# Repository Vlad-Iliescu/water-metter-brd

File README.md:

# water-metter-brd 

full board for capturing water meter image and sending it via wi-fi

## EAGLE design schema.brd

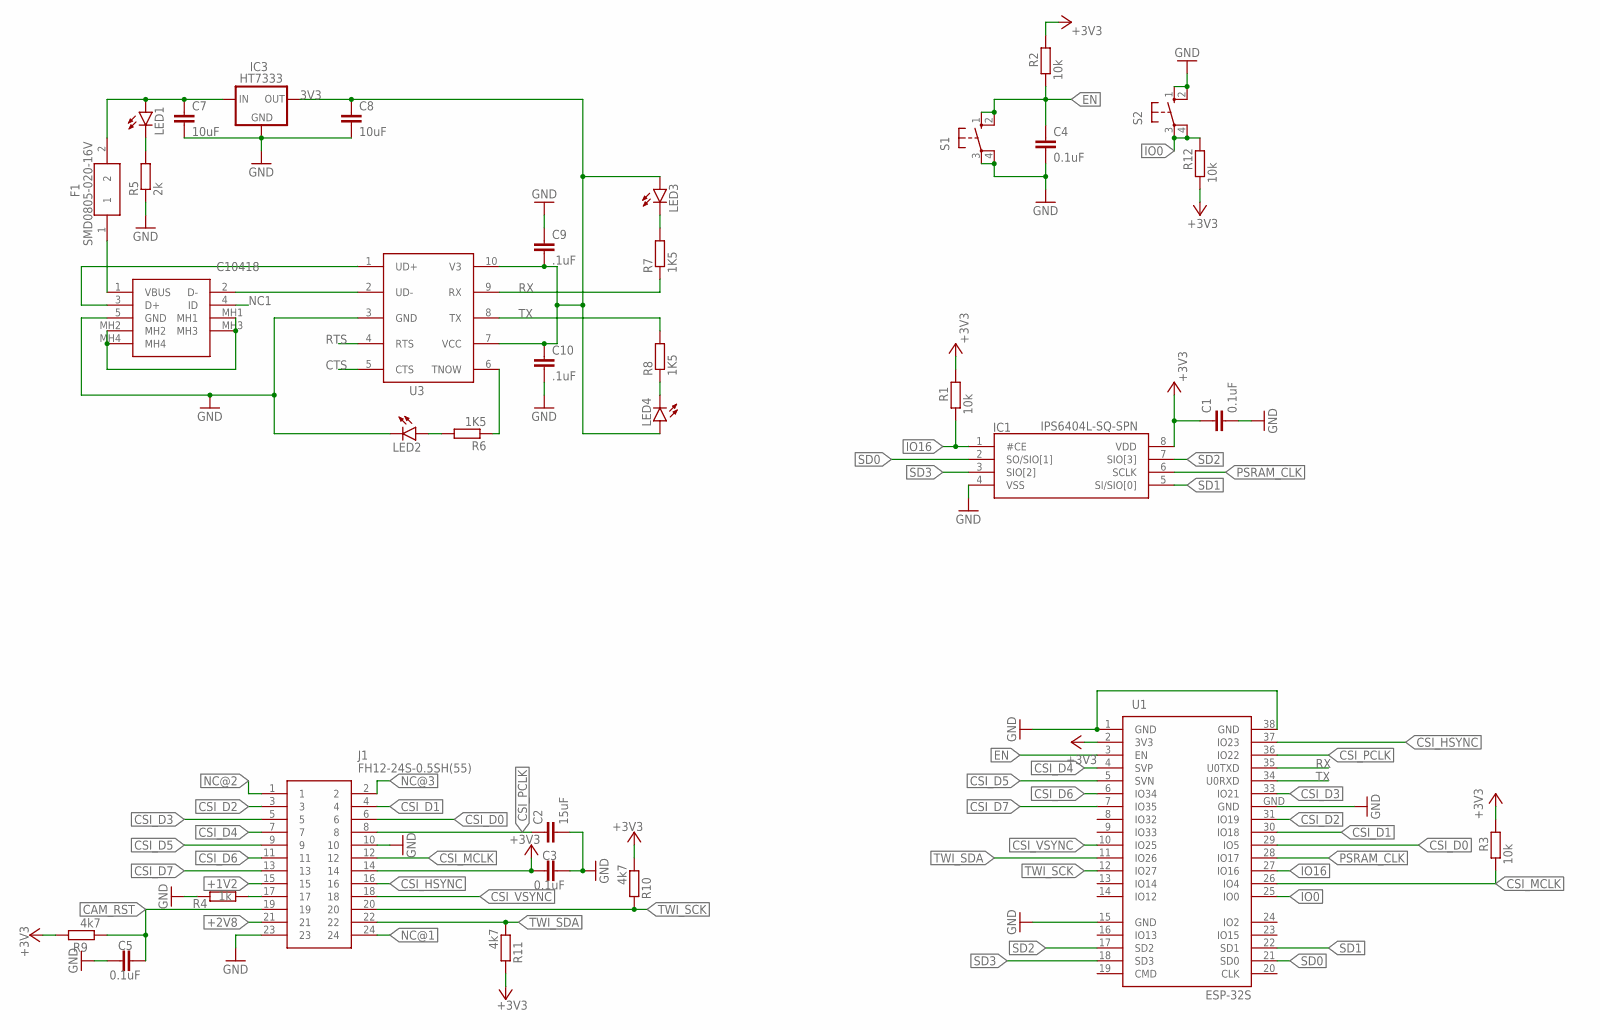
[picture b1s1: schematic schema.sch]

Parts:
C1, C3, C4, C5: 0.1uF; C0805
C2: 15uF; C0805
C7, C8: 10uF; C0805
C9, C10: .1uF; C0805
F1: SMD0805-020-16V; FUSC2114X100N
IC1: IPS6404L-SQ-SPN; SOIC127P600X175-8N
IC3: HT7333; SOT-89
J1: FH12-24S-0.5SH(55)
J3: C10418
LED1, LED2, LED3, LED4: LEDCHIP-LED0805; CHIP-LED0805
R1, R2, R3, R12: 10k; R0805
R4: 1k; R0805
R5: 2k; R0805
R6, R7, R8: 1K5; R0805
R9, R10, R11: 4k7; R0805
S1, S2: 10-XX; B3F-10XX
U1: ESP-32S
U3: CH340ESMD; MSOP10

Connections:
3V3: C8.1, C9.2, C10.1, IC3.1 (OUT), LED3.A, LED4.A, U3.7 (VCC), U3.10 (V3)
5V-USB: F1.1, J3.1 (VBUS)
+1V2: J1.15
+2V8: J1.21
+3V3: C1.1, C3.1, IC1.8 (VDD), J1.14, R1.2, R2.2, R3.2, R9.2, R10.1, R11.2, R12.1, U1.2 (3V3)
+5V1: C7.1, F1.2, IC3.3 (IN), IC3.4 (IN), LED1.A
CAM_RST: C5.2, J1.19, R9.1
CSI_D0: J1.6, U1.29 (IO5)
CSI_D1: J1.4, U1.30 (IO18)
CSI_D2: J1.3, U1.31 (IO19)
CSI_D3: J1.5, U1.33 (IO21)
CSI_D4: J1.7, U1.4 (SVP)
CSI_D5: J1.9, U1.5 (SVN)
CSI_D6: J1.11, U1.6 (IO34)
CSI_D7: J1.13, U1.7 (IO35)
CSI_HSYNC: J1.16, U1.37 (IO23)
CSI_MCLK: J1.12, R3.1, U1.26 (IO4)
CSI_PCLK: C2.1, J1.8, U1.36 (IO22)
CSI_VSYNC: J1.18, U1.10 (IO25)
CTS: U3.5 (CTS)
D+1: J3.3 (D+), U3.1 (UD+)
D-1: J3.2 (D-), U3.2 (UD-)
EN: C4.1, R2.1, S1.1 (S), S1.2 (S1), U1.3 (EN)
GND: C1.2, C2.2, C3.2, C4.2, C5.1, C7.2, C8.2, C9.1, C10.2, IC1.4 (VSS), IC3.2 (GND), J1.10, J1.23, J3.5 (GND), LED2.C, R4.2, R5.1, S1.3, S1.4 (P1), S2.1 (S), S2.2 (S1), U1.1 (GND), U1.15 (GND), U1.38 (GND), U1.GND, U3.3 (GND)
IO0: R12.2, S2.3, S2.4 (P1), U1.25 (IO0)
IO16: IC1.1 (#CE), R1.1, U1.27 (IO16)
MH: J3.MH1, J3.MH2, J3.MH3, J3.MH4
unnamed: J1.17, R4.1
unnamed: LED1.C, R5.2
unnamed: R6.1, U3.6 (TNOW)
unnamed: LED2.A, R6.2
unnamed: LED3.C, R7.2
unnamed: LED4.C, R8.1
NC1: J3.4 (ID)
NC@1: J1.24
NC@2: J1.1
NC@3: J1.2
PSRAM_CLK: IC1.6 (SCLK), U1.28 (IO17)
RTS: U3.4 (RTS)
RX: R7.1, U1.35 (U0TXD), U3.9 (RX)
SD0: IC1.2 (SO/SIO[1]), U1.21 (SD0)
SD1: IC1.5 (SI/SIO[0]), U1.22 (SD1)
SD2: IC1.7 (SIO[3]), U1.17 (SD2)
SD3: IC1.3 (SIO[2]), U1.18 (SD3)
TWI_SCK: J1.20, R10.2, U1.12 (IO27)
TWI_SDA: J1.22, R11.1, U1.11 (IO26)
TX: R8.2, U1.34 (U0RXD), U3.8 (TX)

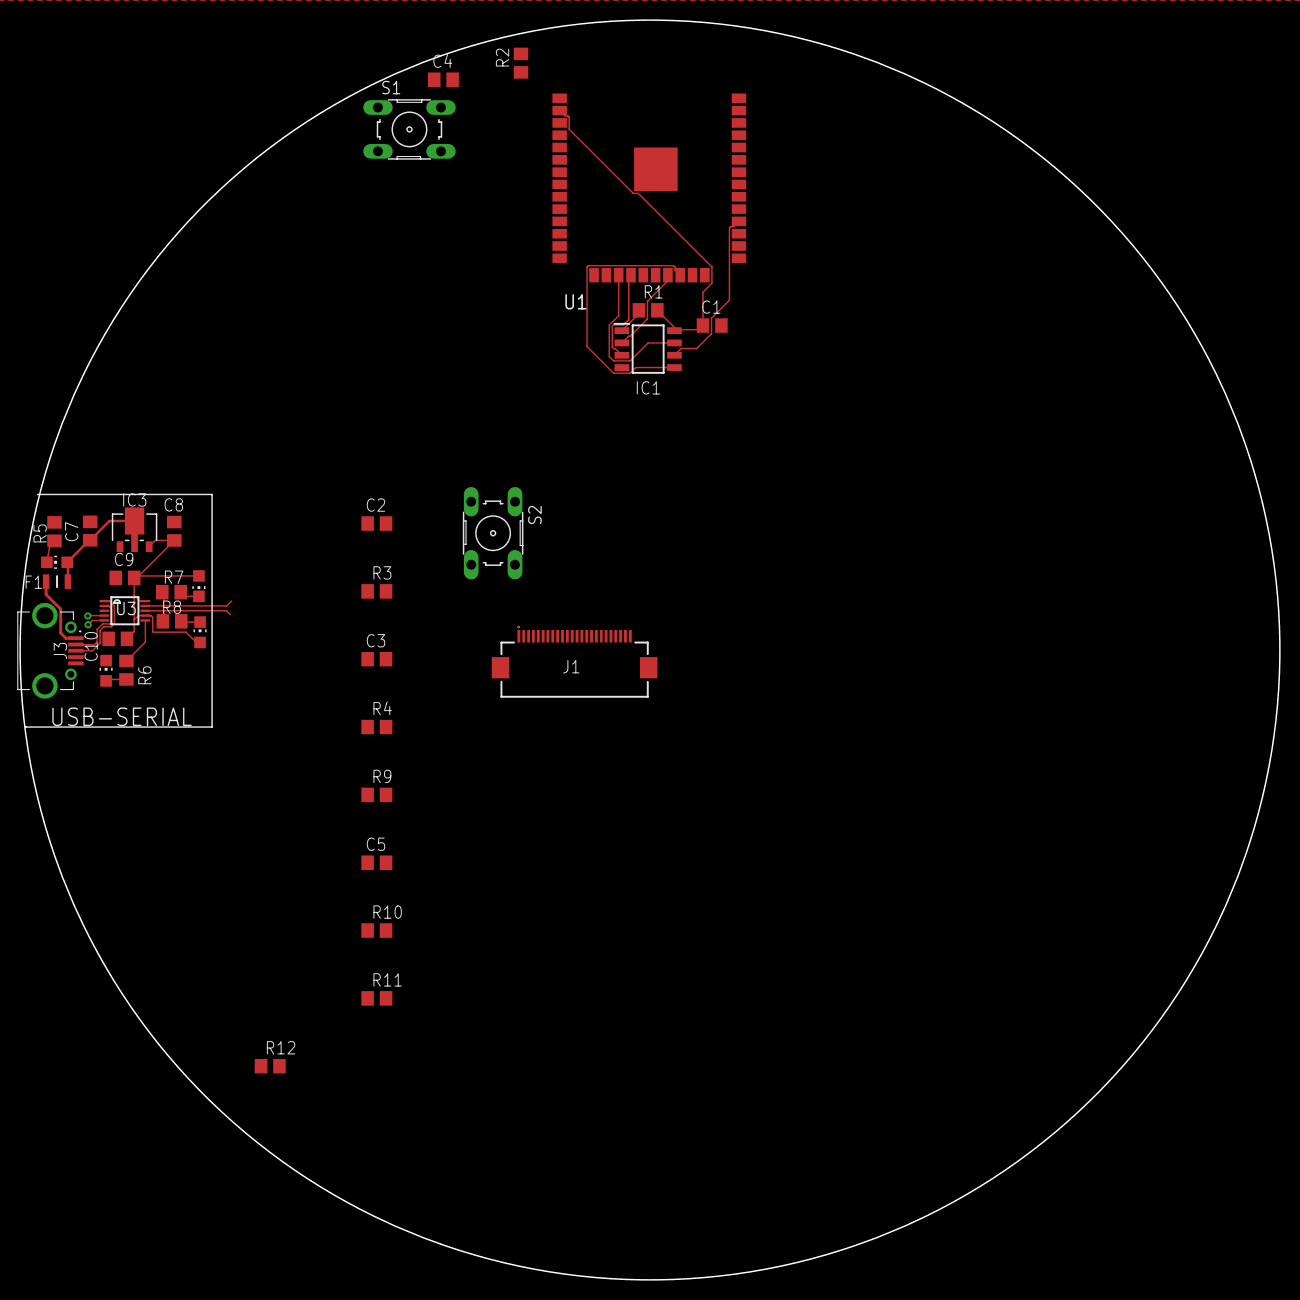
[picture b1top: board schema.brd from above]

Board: 2 copper layers, 130.0 x 130.0 mm, 34 parts (0 on the bottom side), 39 nets.

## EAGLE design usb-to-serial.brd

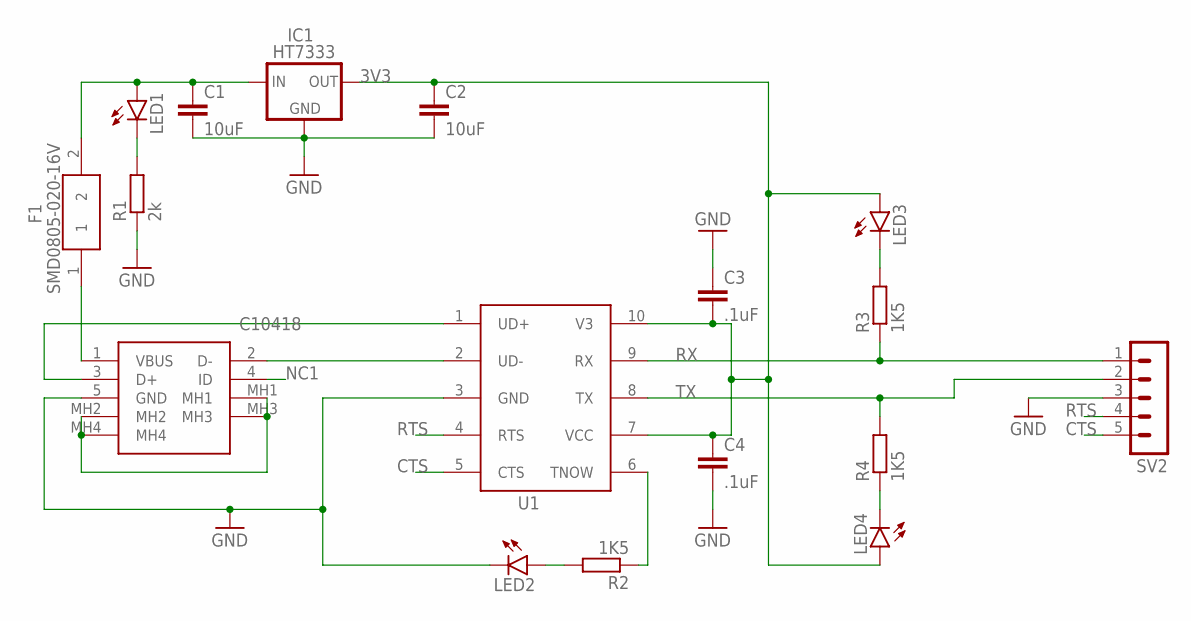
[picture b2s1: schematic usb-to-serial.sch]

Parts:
C1, C2: 10uF; C0805
C3, C4: .1uF; C0805
F1: SMD0805-020-16V; FUSC2114X100N
IC1: HT7333; SOT-89
J1: C10418
LED1, LED2, LED3, LED4: LEDCHIP-LED0805; CHIP-LED0805
R1: 2k; R0805
R2, R3, R4: 1K5; R0805
SV2: MA05-1
U1: CH340ESMD; MSOP10

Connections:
3V3: C2.1, C3.2, C4.1, IC1.1 (OUT), LED3.A, LED4.A, U1.7 (VCC), U1.10 (V3)
+5V: C1.1, F1.2, IC1.3 (IN), IC1.4 (IN), LED1.A
CTS: SV2.5, U1.5 (CTS)
D+: J1.3 (D+), U1.1 (UD+)
D-: J1.2 (D-), U1.2 (UD-)
GND: C1.2, C2.2, C3.1, C4.2, IC1.2 (GND), J1.5 (GND), LED2.C, R1.1, SV2.3, U1.3 (GND)
MH: J1.MH1, J1.MH2, J1.MH3, J1.MH4
unnamed: F1.1, J1.1 (VBUS)
unnamed: LED1.C, R1.2
unnamed: R2.1, U1.6 (TNOW)
unnamed: LED2.A, R2.2
unnamed: LED3.C, R3.2
unnamed: LED4.C, R4.1
NC1: J1.4 (ID)
RTS: SV2.4, U1.4 (RTS)
RX: R3.1, SV2.1, U1.9 (RX)
TX: R4.2, SV2.2, U1.8 (TX)

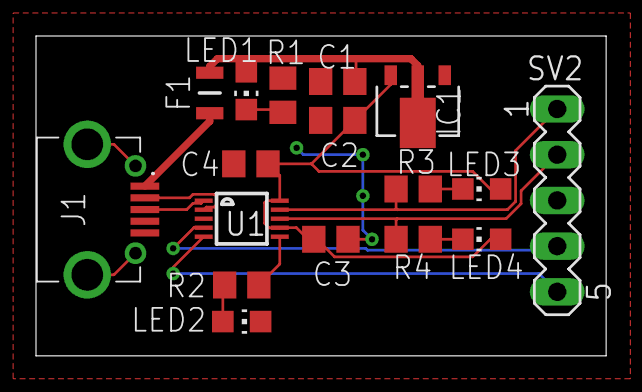
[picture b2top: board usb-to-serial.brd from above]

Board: 2 copper layers, 31.7 x 17.8 mm, 17 parts (0 on the bottom side), 16 nets.

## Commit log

2019-08-16 parts update
2019-08-17 5v dc/dc
2019-09-06 Added new components
2019-09-06 USB to Serial
2019-09-25 USB to Serial done
2019-09-25 Added FUse 0805 to lib
2019-09-25 Added pin header
2019-09-26 Added schema and board pdf/png + Readme
2019-09-30 Added USB-Serial to main design
2019-09-30 Added PSRAM
2019-10-01 CAM ribbon connection
2019-10-02 KiCad start
2019-10-02 battery holder
2019-10-03 battery protection + buckboost
2019-10-04 boost, LDOs, ribbon connerctions
2019-10-05 ribbon connections and reset sw
2019-10-05 removed .DS_Store
2019-10-05 updated gitignore
2019-10-05 SD card
2019-10-06 SD passive and wires
2019-10-07 LED and few connection
2019-10-07 LED SMD
2019-10-07 DRC Fix
2019-10-07 SD Slot Fix
2019-10-07 Small fixes
2019-10-08 Mounting holes and test points
2019-10-08 BOM parts
2019-10-09 BOM parts 2
2019-10-09 refactor
2019-10-10 ALPHA 1
2019-10-10 dimensions
2019-10-10 Added PDFs
2019-10-10 Added render
2019-11-02 added battery charging
2019-11-06 Smaller battery holder
2019-11-23 usb-c
2019-11-23 schematic
2019-11-24 usb-c rev-1 rc
2019-11-24 usb-c rev-1 rc1
2019-12-26 added C167321 usb c
2019-12-26 changed usb part
2020-01-06 battery changing urb c
2020-03-18 switch RTC <-> CTS
